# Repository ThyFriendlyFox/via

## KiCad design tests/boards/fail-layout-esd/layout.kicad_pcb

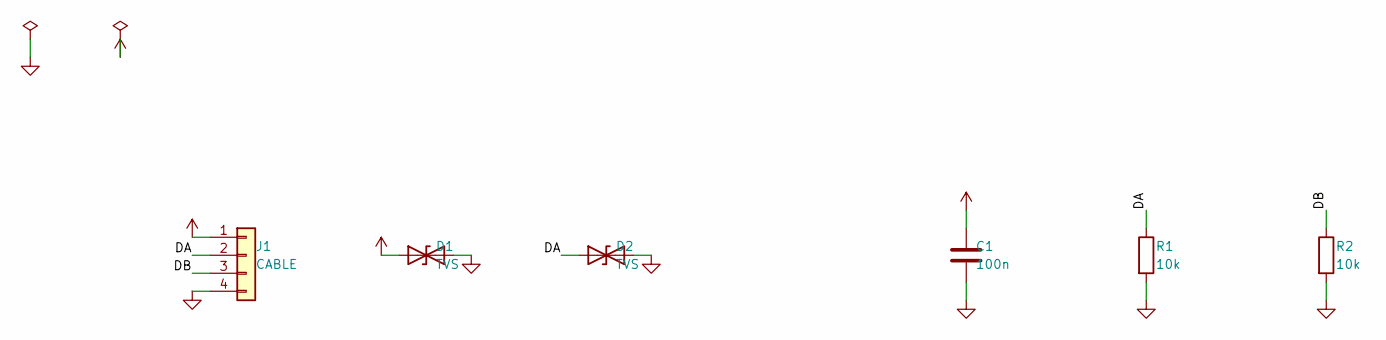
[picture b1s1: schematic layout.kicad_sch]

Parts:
C1: 100n; C_0805_2012Metric
D1, D2: TVS; D_SOD-323
J1: CABLE; PinHeader_1x04_P2.54mm_Vertical
R1, R2: 10k; R_0805_2012Metric

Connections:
/DA: D2.1 (A1), J1.2, R1.1
/DB: J1.3, R2.1
GND: C1.2, D1.2 (A2), D2.2 (A2), J1.4, R1.2, R2.2
VBUS: C1.1, D1.1 (A1), J1.1

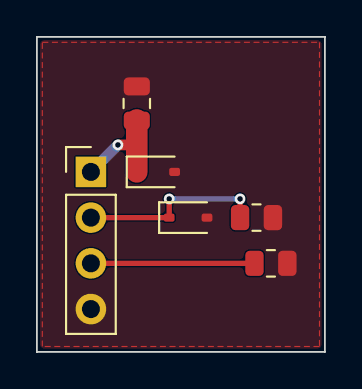
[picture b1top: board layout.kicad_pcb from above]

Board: 2 copper layers, 16.0 x 17.5 mm, 6 parts (0 on the bottom side), 4 nets.

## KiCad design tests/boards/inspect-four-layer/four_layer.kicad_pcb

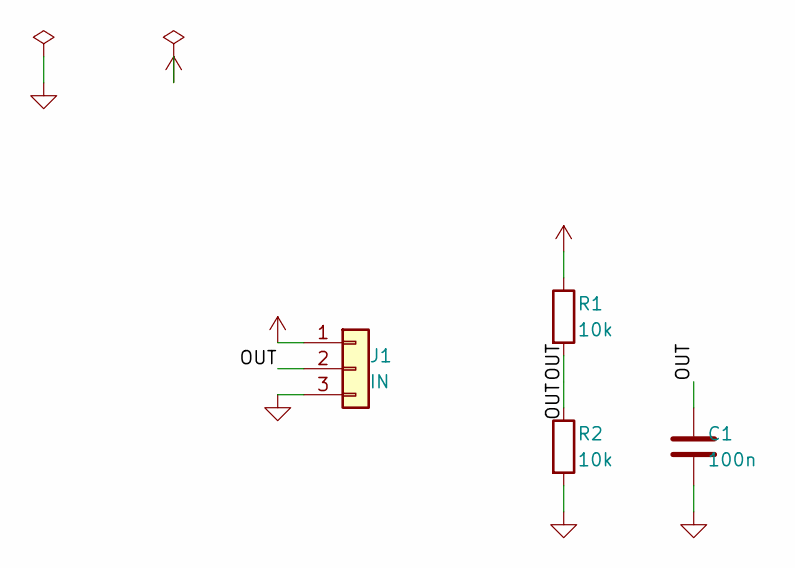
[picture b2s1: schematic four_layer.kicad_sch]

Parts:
C1: 100n; C_0805_2012Metric
J1: IN; PinHeader_1x03_P2.54mm_Vertical
R1, R2: 10k; R_0805_2012Metric

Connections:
/OUT: C1.1, J1.2, R1.2, R2.1
GND: C1.2, J1.3, R2.2
VIN: J1.1, R1.1

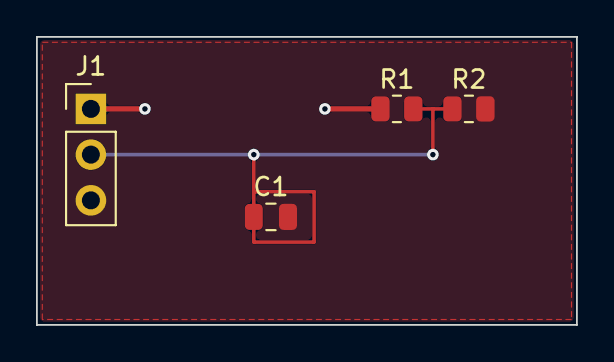
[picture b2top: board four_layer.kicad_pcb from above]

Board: 4 copper layers, 30.0 x 16.0 mm, 4 parts (0 on the bottom side), 3 nets.

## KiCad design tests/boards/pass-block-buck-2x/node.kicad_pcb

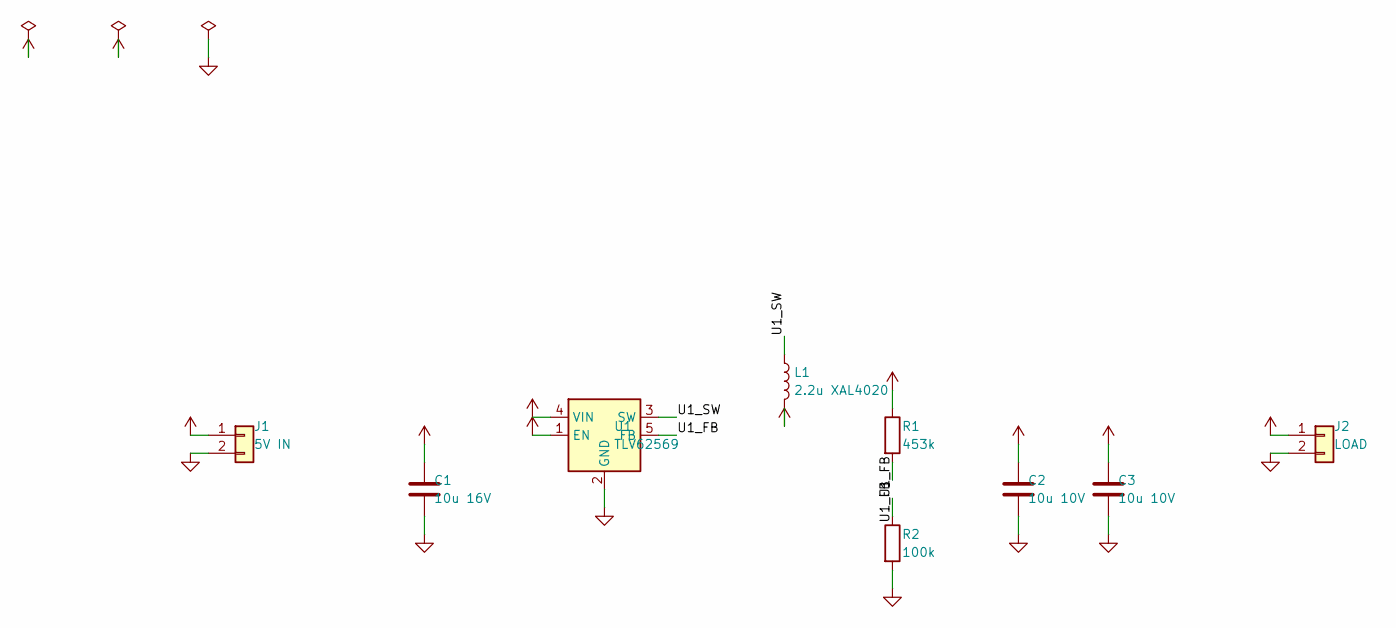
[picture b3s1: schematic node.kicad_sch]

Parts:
C1: 10u 16V; C_0805_2012Metric
C2, C3: 10u 10V; C_0603_1608Metric
J1: 5V IN; PinHeader_1x02_P2.54mm_Vertical
J2: LOAD; PinHeader_1x02_P2.54mm_Vertical
L1: 2.2u XAL4020; L_Coilcraft_XAL4020-XXX
R1: 453k; R_0603_1608Metric
R2: 100k; R_0603_1608Metric
U1: TLV62569; SOT-23-5

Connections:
+3V3: C2.1, C3.1, J2.1, L1.2, R1.1
+5V: C1.1, J1.1, U1.1 (EN), U1.4 (VIN)
/U1_FB: R1.2, R2.1, U1.5 (FB)
/U1_SW: L1.1, U1.3 (SW)
GND: C1.2, C2.2, C3.2, J1.2, J2.2, R2.2, U1.2 (GND)

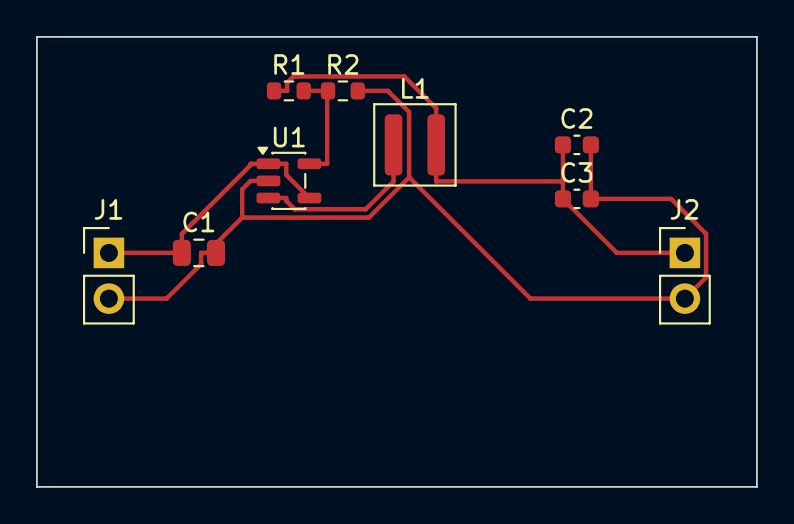
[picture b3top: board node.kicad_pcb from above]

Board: 2 copper layers, 40.0 x 25.0 mm, 9 parts (0 on the bottom side), 5 nets.

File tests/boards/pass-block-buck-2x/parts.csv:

Value,Footprint,Qty,Manufacturer,MPN,Supplier,SKU,Pack,Breaks
TLV62569,Package_TO_SOT_SMD:SOT-23-5,1,Texas Instruments,TLV62569DBVR,,,,
2.2u XAL4020,Inductor_SMD:L_Coilcraft_XAL4020-XXX,1,Coilcraft,XAL4020-222MEC,,,,
453k,Resistor_SMD:R_0603_1608Metric,1,Vishay,CRCW0603453KFKEA,,,,
100k,Resistor_SMD:R_0603_1608Metric,1,Vishay,CRCW0603100KFKEA,,,,
10u 16V,Capacitor_SMD:C_0805_2012Metric,1,made up,FIXTURE-10U-16V,,,,
10u 10V,Capacitor_SMD:C_0603_1608Metric,2,Samsung,CL10A106KP8NNN,,,,

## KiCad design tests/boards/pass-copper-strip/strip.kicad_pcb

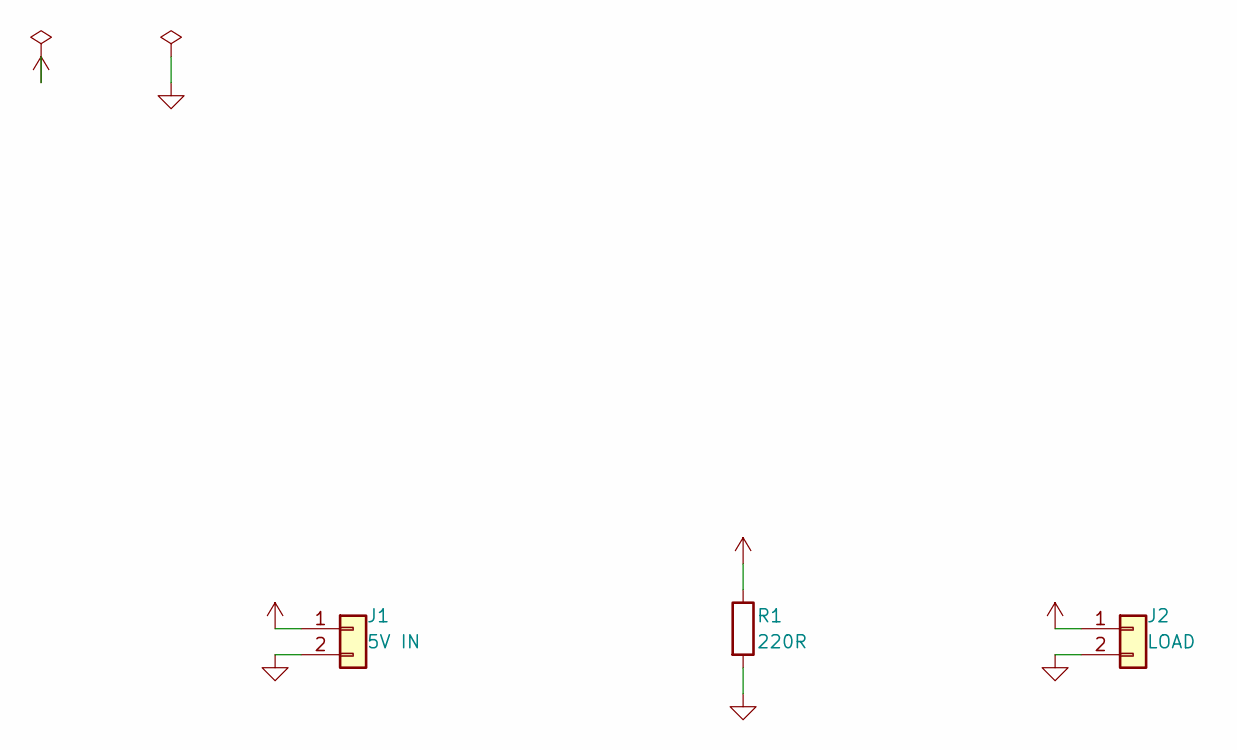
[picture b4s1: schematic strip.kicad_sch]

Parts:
J1: 5V IN; PinHeader_1x02_P2.54mm_Vertical
J2: LOAD; PinHeader_1x02_P2.54mm_Vertical
R1: 220R; R_2512_6332Metric

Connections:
+5V: J1.1, J2.1, R1.1
GND: J1.2, J2.2, R1.2

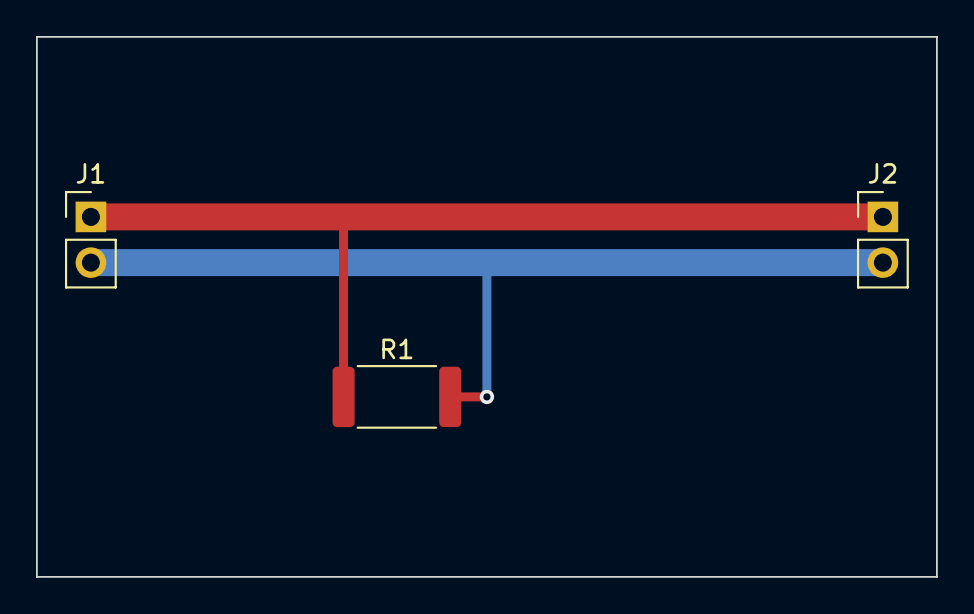
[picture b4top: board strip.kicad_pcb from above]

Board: 2 copper layers, 50.0 x 30.0 mm, 3 parts (0 on the bottom side), 2 nets.
